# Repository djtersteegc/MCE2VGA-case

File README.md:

Yet another case design for the MCE2VGA version 2.0 PCB available from https://sites.google.com/site/tandycocoloco/mda-cga-ega-to-vga.  Wanted something with a more enclosed case than the current designs out there.  All required switchs, buttons, and LED's are brought to the top of case with extenders and light pipes. Only the DIP switch requires a small tool like a mini screwdriver to adjust settings.

# Printing and Assembly

Optimized to print at 0.2mm layer heights with no supports needed.  Print four of the **mce2vga-button-adjust** buttons, and five of the light pipes in a clear filament like nartural PLA, and one of everything else.  The light pipes are press fit with a small lip on the top so make sure to align them correctly in the holes. Assemble with four M3x8mm (or longer) taper head screws. Clearances are tight, so you may have to drill out the button holes with a 5mm bit to get a perfect hole.

# Design Files

STEP models of the MCE2VGA and CoreEP4CE6 boards are in the **KiCad** directory.  Design was done in [DesignSpark Mechanical 6.0](https://www.rs-online.com/designspark/mechanical-software) if you want modify it further.

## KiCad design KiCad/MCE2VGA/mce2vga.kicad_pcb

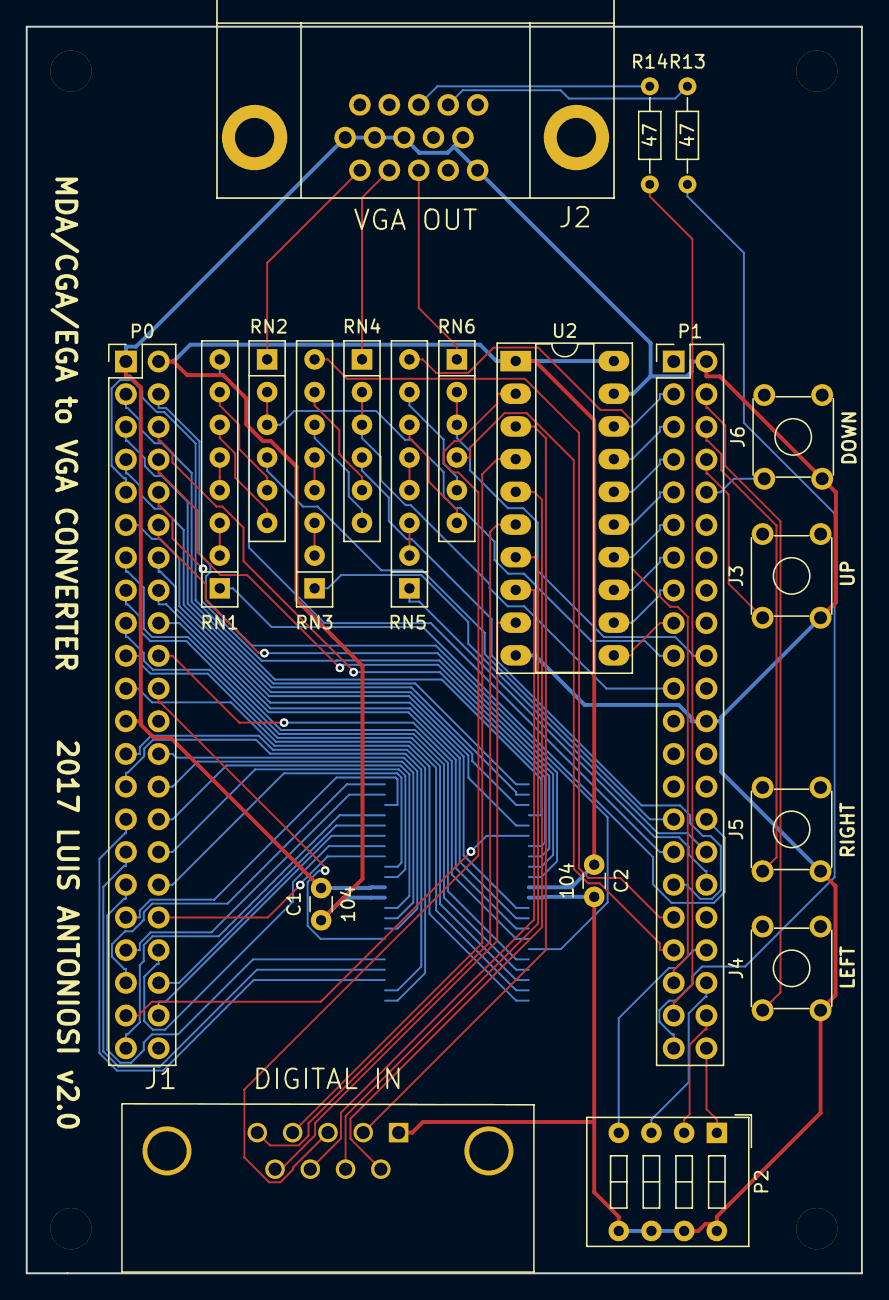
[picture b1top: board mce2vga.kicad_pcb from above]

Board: 2 copper layers, 64.9 x 96.8 mm, 25 parts (1 on the bottom side), 96 nets.

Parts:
C1, C2: 104; C_Disc_D3.0mm_W1.6mm_P2.50mm
J1: DIGITAL IN; DB9F
J2: VGA OUT; HD15_B-HD15F
J3, J4, J5, J6: Conn_02x02_Counter_Clockwise; SW_TH_Tactile_Omron_B3F-10xx
P0, P1: CONN_02X22; Pin_Header_Straight_2x22_Pitch2.54mm
P2: SW1; SW_DIP_x4_W7.62mm_Slide
P3, P4, P5, P6: MOUNT_HOLE; MountingHole_3.2mm_M3
R13, R14: 47; R_Axial_DIN0204_L3.6mm_D1.6mm_P7.62mm_Horizontal
RN1, RN3, RN5: R_Pack04_SIP; R_Array_SIP8
RN2, RN4, RN6: R_Network05; R_Array_SIP6
U1: AS7C34098A; SOP80P1176X120-44N
U2: 74LVC245; DIP-20_W7.62mm_Socket_LongPads

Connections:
B0: P1.34, RN5.1
B1: P1.39, RN5.8
B2: P1.37, RN6.4
B3: P1.20, RN6.2, RN6.3
BLUE: J2.3, RN6.1
DOWN: J6.1, P1.10
G0: P1.32, RN3.1
G1: P1.35, RN3.8
G2: P1.33, RN4.4
G3: P1.21, RN4.2, RN4.3
GND: C1.2, C2.2, J1.1, J2.5, J2.6, J2.7, J2.8, J2.10, J3.3, J4.3, J5.3, J6.3, P0.1, P0.23, P1.2, P1.24, P2.5, P2.6, P2.7, P2.8, U1.12, U1.34, U2.10, U2.19
GREEN: J2.2, RN4.1
H: J1.8, U2.8
HS: J2.13, R14.1
HSYNC: P1.41, R14.2
H_25: P1.15, U2.12
LEFT: J4.1, P1.4
unnamed: RN1.2, RN1.3
unnamed: RN1.4, RN1.5
unnamed: RN1.6, RN2.6
unnamed: RN1.7, RN2.5
unnamed: RN3.2, RN3.3
unnamed: RN3.4, RN3.5
unnamed: RN3.6, RN4.6
unnamed: RN3.7, RN4.5
unnamed: RN5.2, RN5.3
unnamed: RN5.4, RN5.5
unnamed: RN5.6, RN6.6
unnamed: RN5.7, RN6.5
PB: J1.5, U2.6
PB_25: P1.11, U2.14
PG: J1.4, U2.4
PG_25: P1.7, U2.16
PR: J1.3, U2.2
PR_25: P1.3, U2.18
R0: P1.30, RN1.1
R1: P1.31, RN1.8
R2: P1.29, RN2.4
R3: P1.19, RN2.2, RN2.3
RED: J2.1, RN2.1
RIGHT: J5.1, P1.6
SB: J1.7, U2.7
SB_25: P1.13, U2.13
SG: J1.6, U2.5
SG_25: P1.9, U2.15
SR: J1.2, U2.3
SRAM_ADDR0: P0.3, U1.1
SRAM_ADDR1: P0.5, U1.2
SRAM_ADDR2: P0.7, U1.3
SRAM_ADDR3: P0.9, U1.4
SRAM_ADDR4: P0.11, U1.5
SRAM_ADDR5: P0.13, U1.18
SRAM_ADDR6: P0.15, U1.19
SRAM_ADDR7: P0.17, U1.20
SRAM_ADDR8: P0.19, U1.21
SRAM_ADDR9: P0.21, U1.22
SRAM_ADDR10: P0.25, U1.23
SRAM_ADDR11: P0.27, U1.24
SRAM_ADDR12: P0.29, U1.25
SRAM_ADDR13: P0.31, U1.26
SRAM_ADDR14: P0.33, U1.27
SRAM_ADDR15: P0.35, U1.42
SRAM_ADDR16: P0.37, U1.43
SRAM_ADDR17: P0.39, U1.44
SRAM_DQ0: P0.6, U1.7
SRAM_DQ1: P0.8, U1.8
SRAM_DQ2: P0.10, U1.9
SRAM_DQ3: P0.12, U1.10
SRAM_DQ4: P0.14, U1.13
SRAM_DQ5: P0.16, U1.14
SRAM_DQ6: P0.18, U1.15
SRAM_DQ7: P0.20, U1.16
SRAM_DQ8: P0.22, U1.29
SRAM_DQ9: P0.26, U1.30
SRAM_DQ10: P0.28, U1.31
SRAM_DQ11: P0.30, U1.32
SRAM_DQ12: P0.32, U1.35
SRAM_DQ13: P0.34, U1.36
SRAM_DQ14: P0.36, U1.37
SRAM_DQ15: P0.38, U1.38
SR_25: P1.5, U2.17
SW0: P1.44, P2.1
SW1: P1.42, P2.2
SW2: P1.40, P2.3
SW3: P1.38, P2.4
UP: J3.1, P1.8
V: J1.9, U2.9
VCC33V: C1.1, C2.1, P0.2, U1.11, U1.33, U2.1, U2.20
VS: J2.14, R13.1
VSYNC: P1.43, R13.2
V_25: P1.17, U2.11
~SRAM_CE: P0.41, U1.6
~SRAM_LB: P0.42, U1.39
~SRAM_OE: P0.43, U1.41
~SRAM_UB: P0.40, U1.40
~SRAM_WE: P0.4, U1.17

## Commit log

2023-02-22 Add light pipes for LED's, tweak opening for on/off switch
